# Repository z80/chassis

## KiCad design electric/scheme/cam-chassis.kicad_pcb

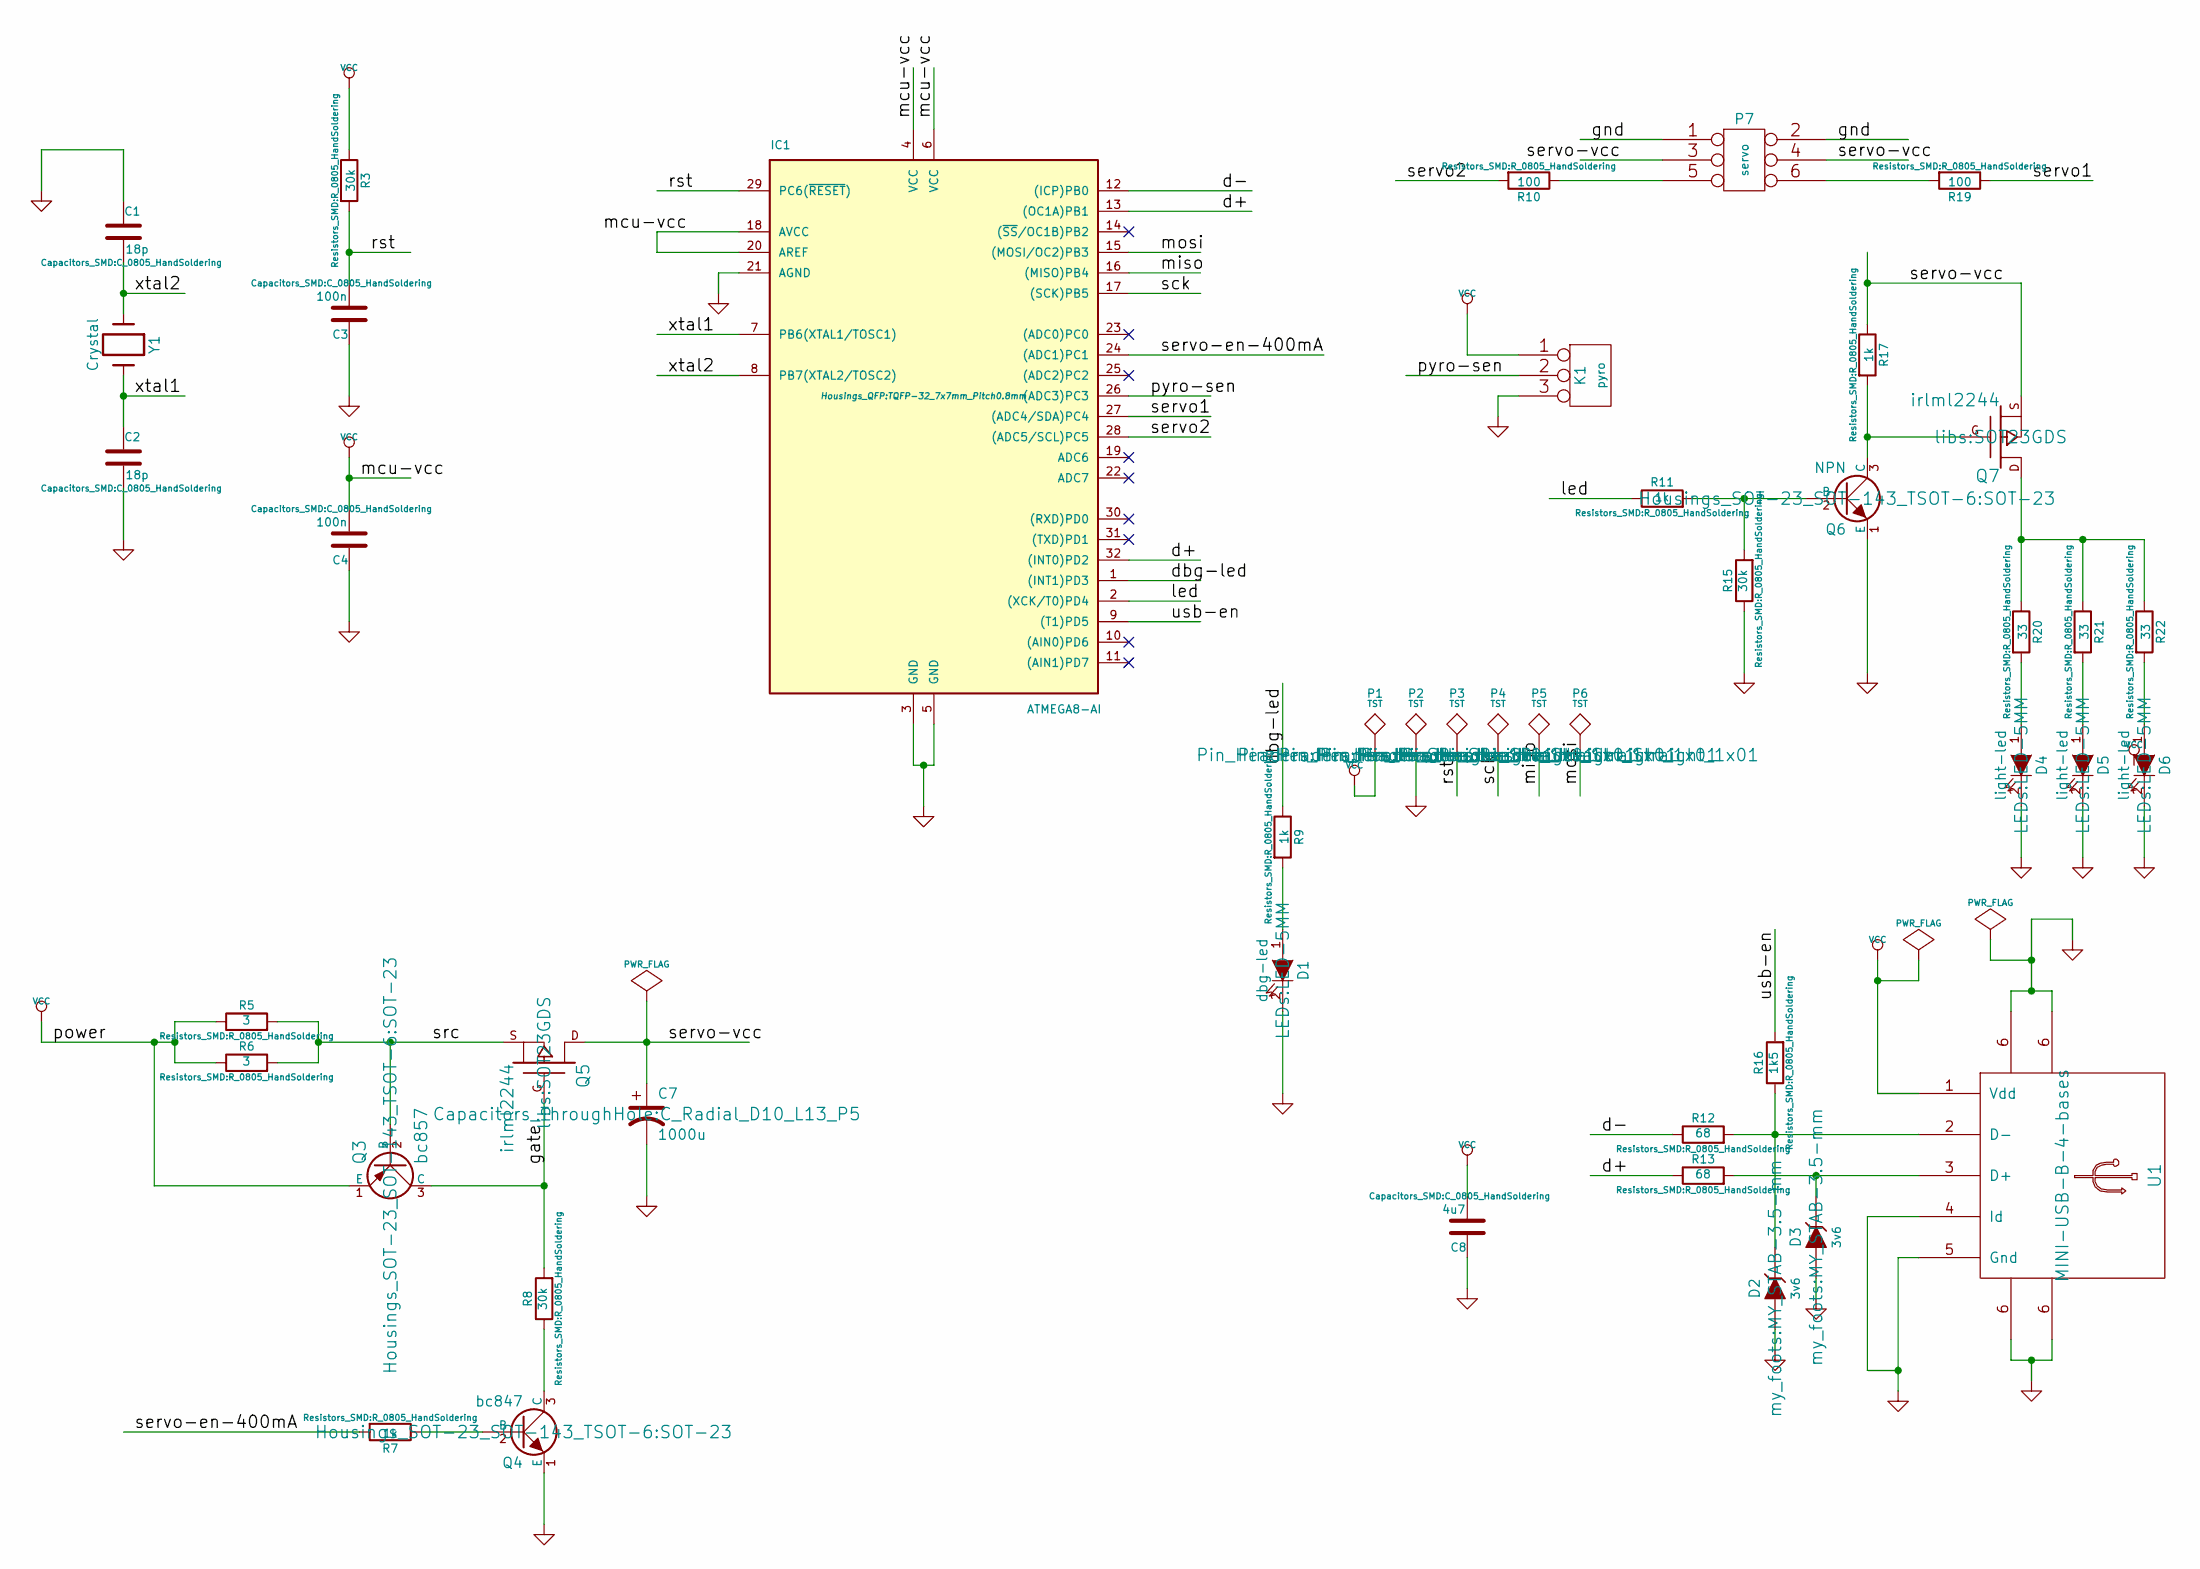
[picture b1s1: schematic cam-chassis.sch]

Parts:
C1, C2: 18p; C_0805_HandSoldering
C3, C4: 100n; C_0805_HandSoldering
C7: 1000u; C_Radial_D10_L13_P5
C8: 4u7; C_0805_HandSoldering
D1: dbg-led; LED-5MM
D2, D3: 3v6; MY_STAB-3.5-mm
D4, D5, D6: light-led; LED-5MM
IC1: ATMEGA8-AI; TQFP-32_7x7mm_Pitch0.8mm
K1: pyro; Pin_Header_Straight_1x03
P1, P2, P3, P4, P5, P6: TST; Pin_Header_Straight_1x01
P7: servo; Pin_Header_Straight_2x03
Q3: bc857; SOT-23
Q4: bc847; SOT-23
Q5, Q7: irlml2244; SOT23GDS
Q6: NPN; SOT-23
R3, R8, R15: 30k; R_0805_HandSoldering
R5, R6: 3; R_0805_HandSoldering
R7, R9, R11, R17: 1k; R_0805_HandSoldering
R10, R19: 100; R_0805_HandSoldering
R12, R13: 68; R_0805_HandSoldering
R16: 1k5; R_0805_HandSoldering
R20, R21, R22: 33; R_0805_HandSoldering
U1: MINI-USB-B-4-bases; USB_Mini-B
Y1: Crystal; Crystal_HC49-U_Vertical

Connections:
/d+: IC1.13 ((OC1A)PB1), IC1.32 ((INT0)PD2), R13.1
/d-: IC1.12 ((ICP)PB0), R12.1
/dbg-led: IC1.1 ((INT1)PD3), R9.1
/gate: Q3.3 (C), Q5.G, R8.2
/led: IC1.2 ((XCK/T0)PD4), R11.1
/miso: IC1.16 ((MISO)PB4), P5.1
/mosi: IC1.15 ((MOSI/OC2)PB3), P6.1
/pyro-sen: IC1.26 ((ADC3)PC3), K1.2 (PM)
/rst: C3.2, IC1.29 (PC6(~RESET~)), P3.1, R3.2
/sck: IC1.17 ((SCK)PB5), P4.1
/servo1: IC1.27 ((ADC4/SDA)PC4), R19.1
/servo2: IC1.28 ((ADC5/SCL)PC5), R10.2
/servo-en-400mA: IC1.24 ((ADC1)PC1), R7.2
/servo-vcc: C7.1, P7.3, P7.4, Q5.D, Q7.S, R17.1
/src: Q3.2 (B), Q5.S, R5.2, R6.2
/usb-en: IC1.9 ((T1)PD5), R16.2
/xtal1: C2.1, IC1.7 (PB6(XTAL1/TOSC1)), Y1.2
/xtal2: C1.2, IC1.8 (PB7(XTAL2/TOSC2)), Y1.1
GND: C1.1, C2.2, C3.1, C4.1, C7.2, C8.1, D1.2 (K), D2.1 (A), D3.1 (A), D4.2 (K), D5.2 (K), D6.2 (K), IC1.3 (GND), IC1.5 (GND), IC1.21 (AGND), K1.3, P2.1, P7.1, P7.2, Q4.1 (E), Q6.1 (E), R15.1, U1.4 (Id), U1.5 (Gnd), U1.6
unnamed: D1.1 (A), R9.2
unnamed: D2.2 (K), R12.2, R16.1, U1.2 (D-)
unnamed: D3.2 (K), R13.2, U1.3 (D+)
unnamed: D4.1 (A), R20.2
unnamed: D5.1 (A), R21.2
unnamed: D6.1 (A), R22.2
unnamed: P7.5, R10.1
unnamed: P7.6, R19.2
unnamed: Q4.2 (B), R7.1
unnamed: Q4.3 (C), R8.1
unnamed: Q6.2 (B), R11.2, R15.2
unnamed: Q6.3 (C), Q7.G, R17.2
unnamed: Q7.D, R20.1, R21.1, R22.1
VCC: C4.2, C8.2, IC1.4 (VCC), IC1.6 (VCC), IC1.18 (AVCC), IC1.20 (AREF), K1.1, P1.1, Q3.1 (E), R3.1, R5.1, R6.1, U1.1 (Vdd)

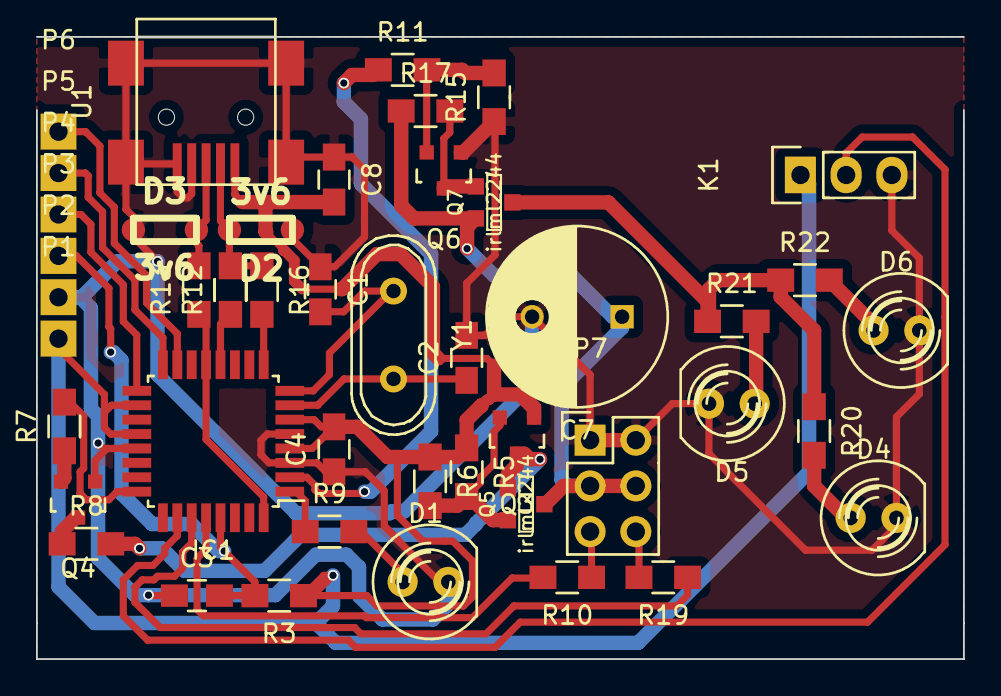
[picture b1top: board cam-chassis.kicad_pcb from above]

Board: 2 copper layers, 51.5 x 34.6 mm, 45 parts (0 on the bottom side), 33 nets.

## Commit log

2015-06-01 initial condition
2015-06-01 Added last (for the moment) 3-d party packets.
2015-06-02 Works.
2015-06-04 Started processes description.
2015-07-08 Now tor starts in the right way.
2015-07-16 Server works but video isn't streamed yet.
2015-07-16 Awesome idea to just use javascript setInterval() and refresh image with just getting it with different parameters. E.i. ?d=.... Where ... some random number to prevent caching image in browser.
2015-07-18 Sending images works.
2015-07-21 Make source JPG with 70 compression ratio.
2015-07-21 Made QSystemTrayIcon.
2015-07-22 Implemented capture in Windows through videoInput library.
2015-07-23 Adjusted setup. It looks like in most cases it works. If it doesn't, it is only necessary to update page.
2015-07-26 Replaced components to the ones I have.
2015-07-26 Removed unnecessary files.
2015-07-29 Prepared SVG.
2015-07-29 Made LEDs power also limited.
2015-07-31 INT0 must be connected to D+ - not D- (!!!)
2015-08-03 Made separate project. LEDs work.
2015-08-03 Still works!
2015-08-03 Now power control looks working as expected.
2015-08-04 Implemented PWM via Timer1. But it should be tested.
2015-08-05 Checked posting to server and jQuery sliders.
2015-08-06 Improved PWM control part by simulating it's behavior.
2015-08-07 Debugging. Pwm hangs USB io.
2015-08-07 All queries work.
2015-08-07 Struggling with checkboxes.
2015-08-08 Made debug blink by timer1. Will test it.
2015-08-09 Servo works.
2015-08-09 Sensor works.
2015-08-09 Web interface works.
2015-08-16 Removed unnecessary controls.
2015-10-15 Added image quality slider.
